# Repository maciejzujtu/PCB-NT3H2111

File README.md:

# PCB-NT3H2111
Schematic for my own PCB of a business card in ISO/IEC 7810:2023 form factor with NFC capabilities.

readme TODO...

If University will not fuck me I will finish it and thr readme

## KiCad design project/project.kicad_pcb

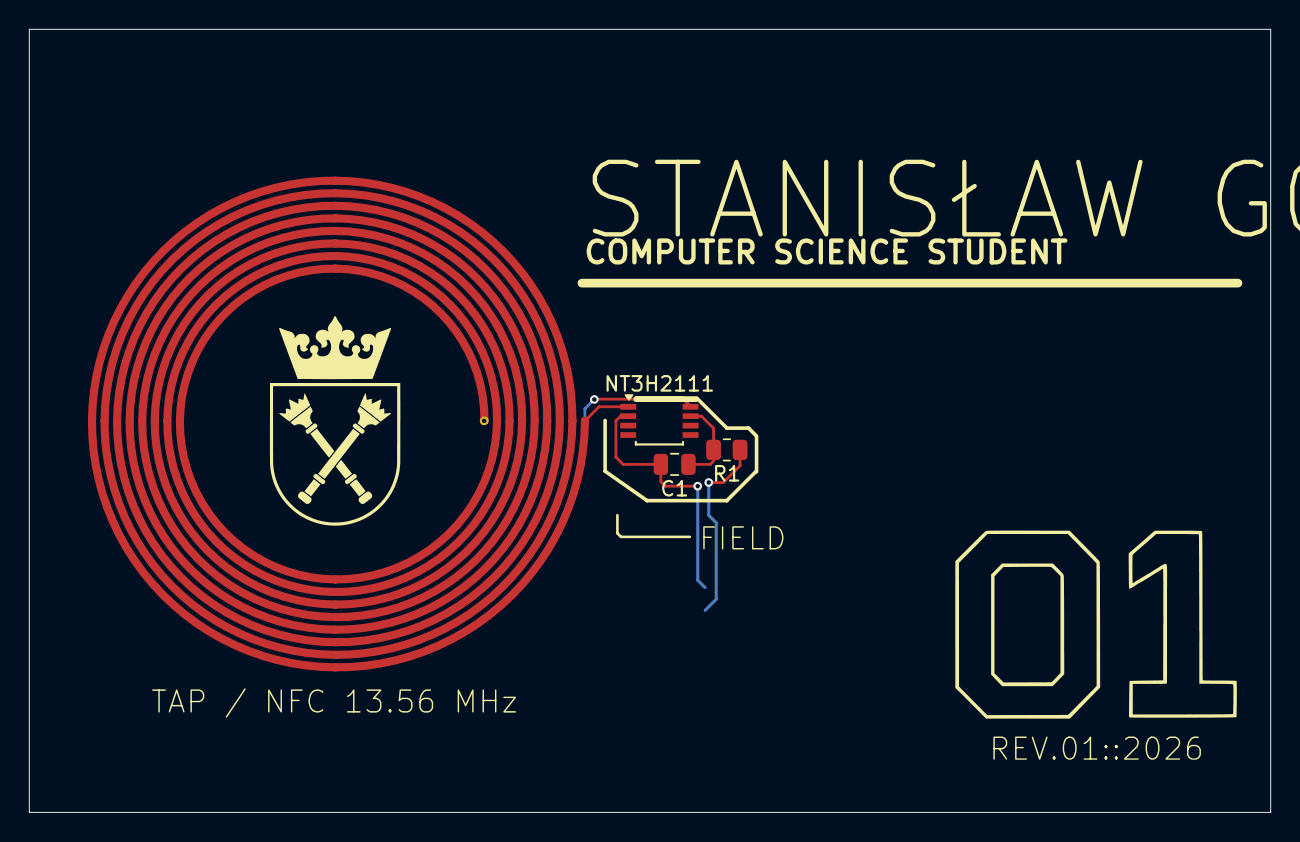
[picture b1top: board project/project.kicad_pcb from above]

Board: 2 copper layers, 85.6 x 54.0 mm, 5 parts (1 on the bottom side), 5 nets.

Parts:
ANT1: Class5_Circular_D35mm_ID20mm_8T_W0.56_G0.30
C1: 220nF; C_0805_2012Metric
LED1: APT1608SYCK/J3-PRV; LED_0603_1608Metric
NT3H2111: TSSOP-8_3x3mm_P0.65mm
R1: 1 kΩ; R_0805_2012Metric

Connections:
GND: C1.2, LED1.1 (K), NT3H2111.2 (VSS)
unnamed: LED1.2 (A), R1.1
unnamed: ANT1.1, NT3H2111.1 (LA)
unnamed: ANT1.2, NT3H2111.8 (LB)
unnamed: C1.1, NT3H2111.7 (VOUT), R1.2

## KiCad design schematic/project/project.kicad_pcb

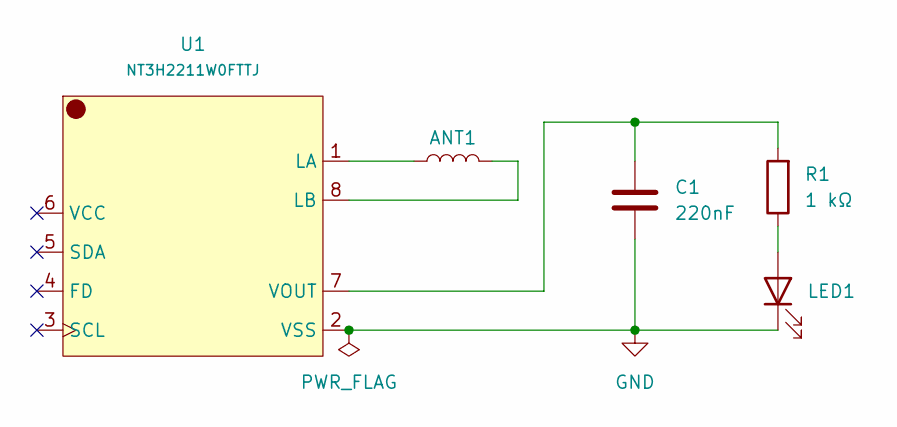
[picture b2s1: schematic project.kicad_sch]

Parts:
ANT1: Class5_Circular_D35mm_ID20mm_8T_W0.56_G0.30
C1: 220nF; C_0805_2012Metric; LCSC Part # C520076
LED1: APT1608SYCK/J3-PRV; LED_0603_1608Metric; LCSC Part # C5440241
R1: 1 kΩ; R_0805_2012Metric; LCSC Part # C17513
U1: NT3H2211W0FTTJ; TSSOP-8_3x3mm_P0.65mm; LCSC Part # C2654822

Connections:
GND: C1.2, LED1.1 (K), U1.2 (VSS)
unnamed: LED1.2 (A), R1.1
unnamed: ANT1.1, U1.1 (LA)
unnamed: ANT1.2, U1.8 (LB)
unnamed: C1.1, R1.2, U1.7 (VOUT)

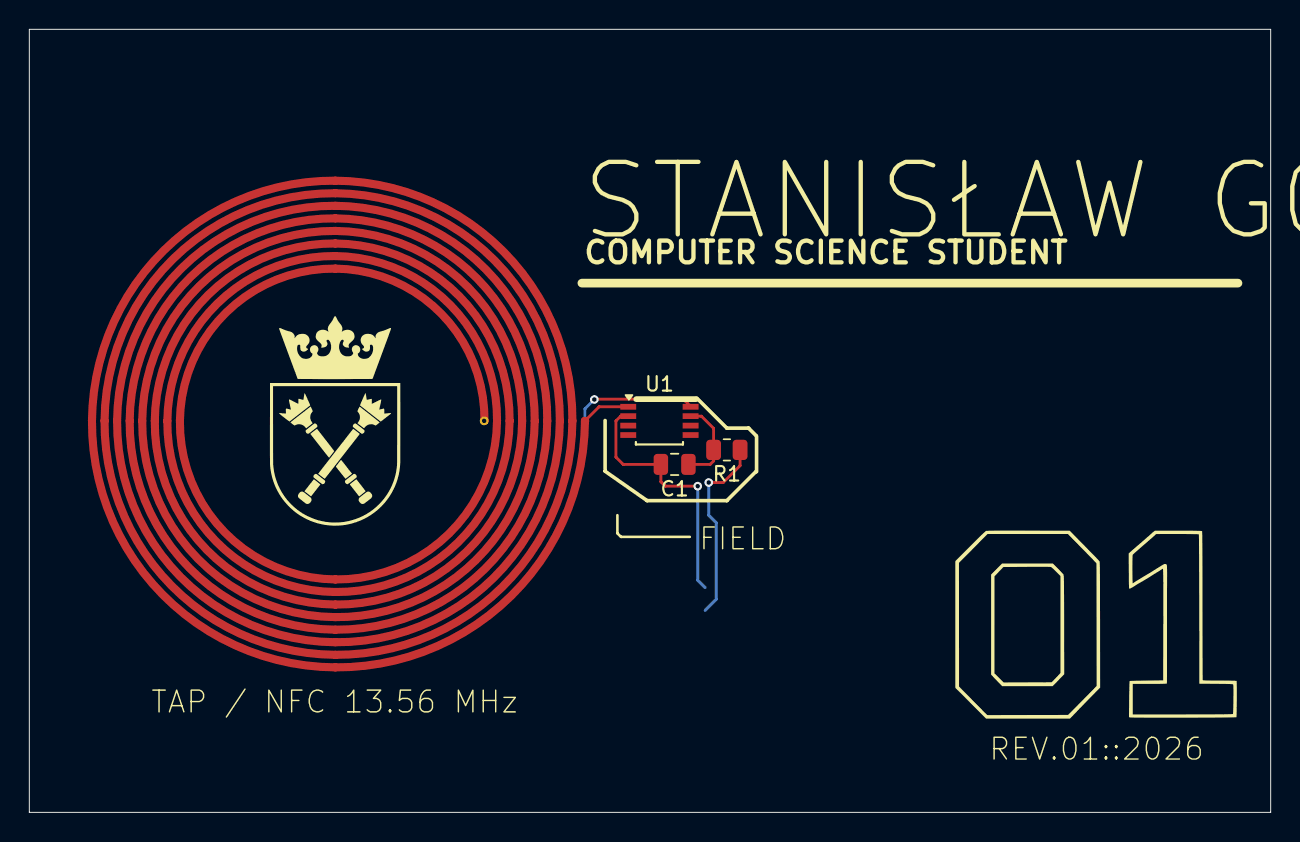
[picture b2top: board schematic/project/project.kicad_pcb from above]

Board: 2 copper layers, 85.6 x 54.0 mm, 5 parts (1 on the bottom side), 5 nets.

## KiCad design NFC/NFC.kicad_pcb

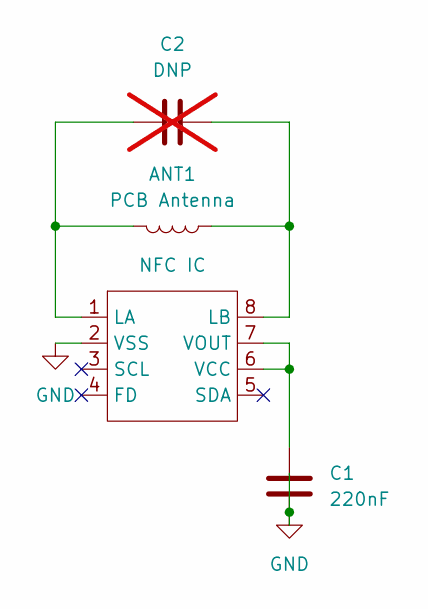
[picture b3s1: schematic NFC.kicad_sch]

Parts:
ANT1: PCB Antenna; Class4_48x25mm_5T
C1: 220nF; C_0805_2012Metric
C2: DNP; C_0805_2012Metric; not fitted
U1: NFC IC; TSSOP-8_3x3mm_P0.65mm

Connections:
GND: C1.2, U1.2 (VSS)
unnamed: ANT1.2, C2.2, U1.1 (LA)
unnamed: ANT1.1, C2.1, U1.8 (LB)
unnamed: C1.1, U1.6 (VCC), U1.7 (VOUT)

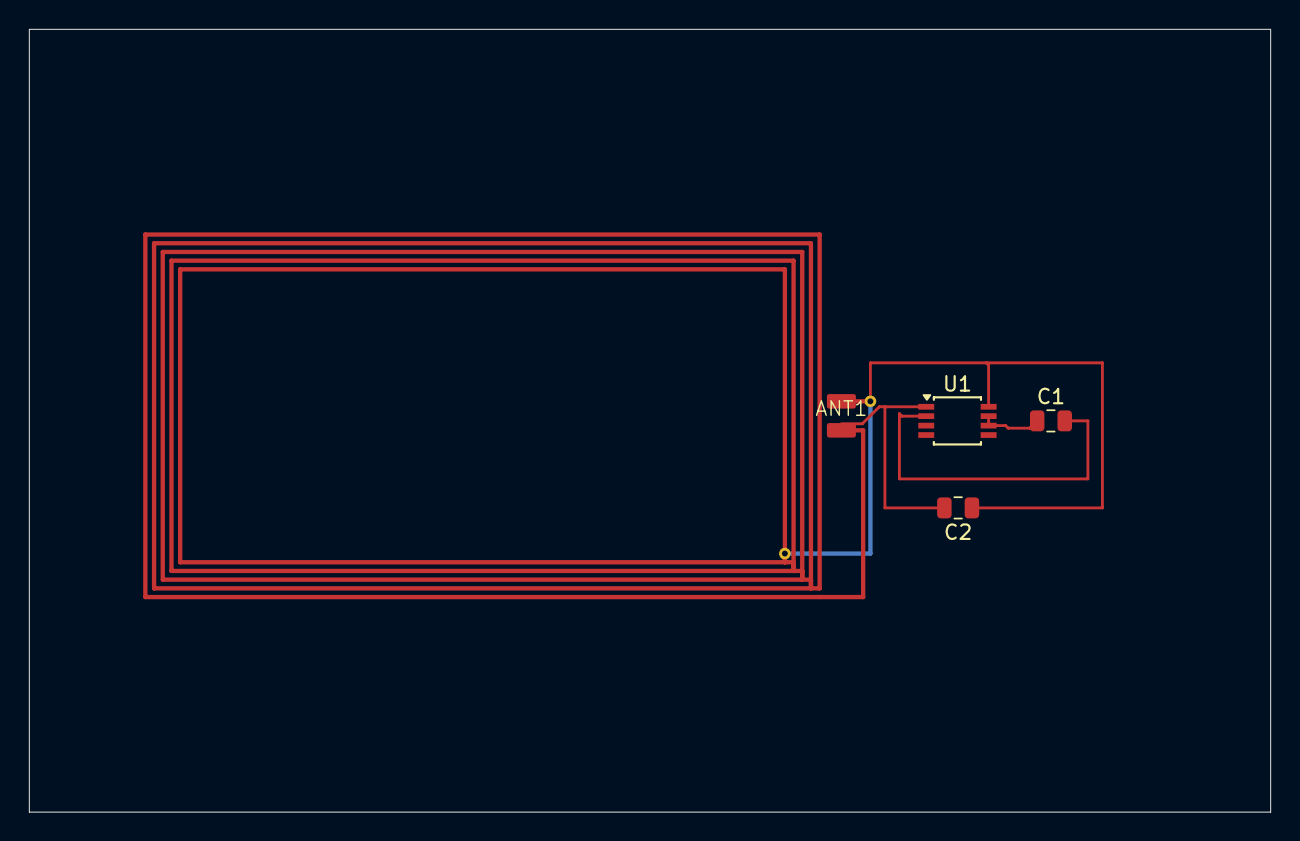
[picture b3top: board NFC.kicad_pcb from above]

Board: 2 copper layers, 85.6 x 54.0 mm, 4 parts (0 on the bottom side), 4 nets.
